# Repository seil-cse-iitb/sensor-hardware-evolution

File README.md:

# Sensor Hardware Evolution

The folder contains 2 versions of hardware design along with their schematics and PCB files. They are designed in **Ki-CAD**.

Both versions have Pro Mini as micro-controller and nRF24L01+ as communication module. In addition to that version 2 has a separate pinout for I2C communication such that any I2C module can be directly mounted on it. It also has a AMS1117 3v3 voltage regulator. Hence, power supplies upto 5 volt can power the node.

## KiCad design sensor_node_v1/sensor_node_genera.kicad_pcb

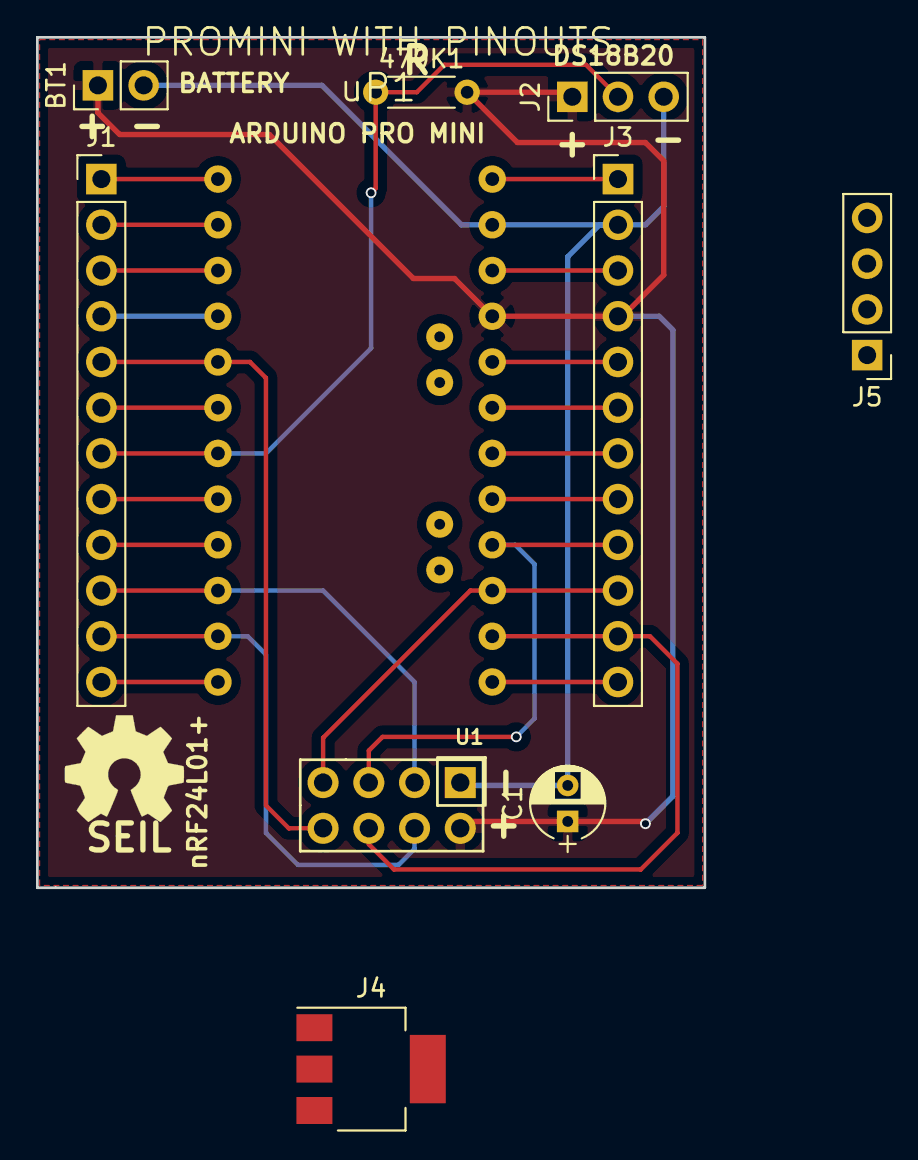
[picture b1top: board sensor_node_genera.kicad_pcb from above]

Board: 2 copper layers, 37.1 x 47.2 mm, 10 parts (0 on the bottom side), 26 nets.

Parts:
470K1: R; R_Axial_DIN0204_L3.6mm_D1.6mm_P5.08mm_Horizontal
BT1: Battery_Cell; Socket_Strip_Straight_1x02_Pitch2.54mm
C1: CP_Small; CP_Radial_D4.0mm_P2.00mm
J1, J3: MALE CONNECTORS; Socket_Strip_Straight_1x12_Pitch2.54mm
J2: PWR SELECT; Socket_Strip_Straight_1x03_Pitch2.54mm
J4: 3V3 REG; SOT-223
J5: I2C Connections; Socket_Strip_Straight_1x04_Pitch2.54mm
U1: nRF24L01+; NRF24L01
uP1: PROMINI WITH PINOUTS; ArduProMini-6

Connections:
/3V3_NRF: C1.1, J2.2, U1.2
/3V3_REG: J2.1, J4.2
/A0: J3.8, uP1.26
/A1: J3.7, uP1.25
/A2: J3.6, uP1.24
/A3: J3.5, uP1.23
/CE: J1.10, U1.3, uP1.16
/CSN: J1.11, U1.4, uP1.17
/D3: J1.6, uP1.12
/D5: J1.8, uP1.14
/D6: J1.9, uP1.15
/D9: J1.12, uP1.18
/D10: J3.12, uP1.30
/DATA: 470K1.1, J1.7, uP1.13
/GND: BT1.2, C1.2, J1.4, J3.2, J4.1, J5.4, U1.1, uP1.10, uP1.20
/IRQ: J1.5, U1.8, uP1.11
/MISO: J3.10, U1.7, uP1.28
/MOSI: J3.11, U1.6, uP1.29
/RAW: J3.1, uP1.19
/RST: J1.3, J3.3, uP1.9, uP1.21
/RX0: J1.2, uP1.8
/SCK: J3.9, U1.5, uP1.27
/SCL: J5.2, uP1.32
/SDA: J5.3, uP1.31
/TX0: J1.1, uP1.7
/VCC: 470K1.2, BT1.1, J2.3, J3.4, J4.3, J5.1, uP1.22

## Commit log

2019-06-11 Uploaded the second version of sensor suite
2019-06-11 Uploaded version 1 of sensor node
2019-06-21 Updated README file
